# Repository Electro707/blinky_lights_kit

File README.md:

# Blinky Lights Kit

Welcome to the main repository for the Blinking Lights Kit. Here you will find everything that was used to make the project/kit come to life, from the KiCad file to the instruction's SVGs.

See [HERE](https://kits.electro707.com/blinky_lights/) for the project's page and documentation (including soldering instructions).

### Kit on Tindie
I am currently selling the kit on Tindie. The product page can be found at [https://www.tindie.com/products/20887/](https://www.tindie.com/products/20887/).

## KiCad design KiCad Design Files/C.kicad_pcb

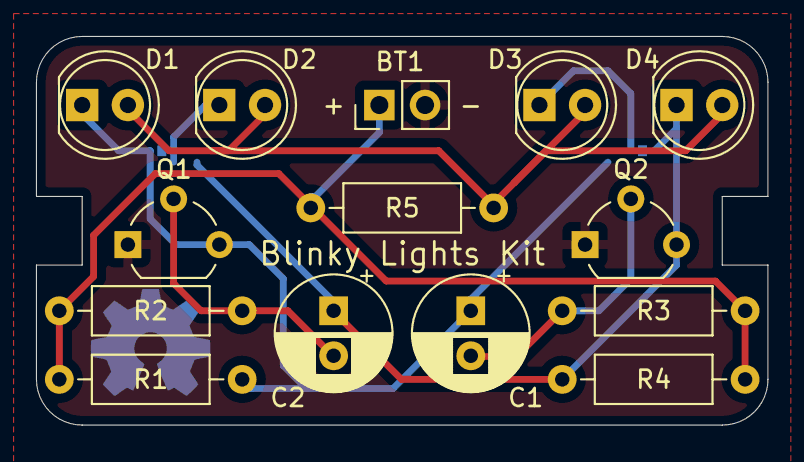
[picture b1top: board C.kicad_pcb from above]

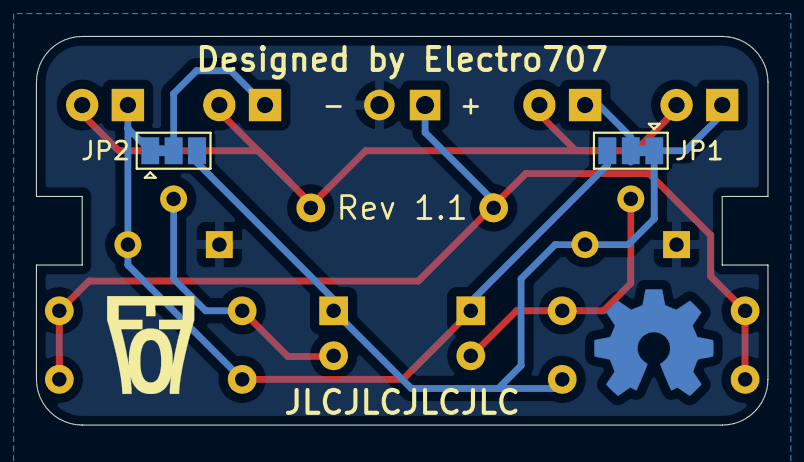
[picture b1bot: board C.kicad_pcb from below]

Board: 2 copper layers, 40.6 x 21.6 mm, 16 parts (2 on the bottom side), 9 nets.

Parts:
BT1: Battery; PinHeader_1x02_P2.54mm_Vertical
C1, C2: 100uF; CP_Radial_D6.3mm_P2.50mm
D1, D2, D3, D4: LED; LED_D5.0mm
JP1, JP2: SolderJumper_3_Bridged12; SolderJumper-3_P1.3mm_Bridged12_Pad1.0x1.5mm
Q1, Q2: 2N3904; TO-92_Wide
R1, R4: 270; R_Axial_DIN0207_L6.3mm_D2.5mm_P10.16mm_Horizontal
R2, R3: 10k; R_Axial_DIN0207_L6.3mm_D2.5mm_P10.16mm_Horizontal
R5: 1k; R_Axial_DIN0207_L6.3mm_D2.5mm_P10.16mm_Horizontal

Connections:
C1: C1.1, D1.1 (K), JP1.1 (A), JP2.3 (B), Q1.3 (C), R1.2
C2: C2.1, D4.1 (K), JP1.3 (B), JP2.1 (A), Q2.3 (C), R4.2
GND: BT1.2 (-), Q1.1 (E), Q2.1 (E)
unnamed: C1.2, Q2.2 (B), R3.2
unnamed: C2.2, Q1.2 (B), R2.2
unnamed: D1.2 (A), D2.2 (A), D3.2 (A), D4.2 (A), R5.2
unnamed: D2.1 (K), JP1.2 (C)
unnamed: D3.1 (K), JP2.2 (C)
VCC: BT1.1 (+), R1.1, R2.1, R3.1, R4.1, R5.1

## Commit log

2020-07-23 Changed README.md
2021-03-10 Oops, forgot to update the Tindie link (also added image on repo's page
2021-12-09 Updated schematic, 100k to 10k. Added right title block
2022-06-19 Updated files to KiCAD 6.0 and updated board to rev 1.1
    Rev 1.1 includes the following changes:
    - Minor silkscreen changes and component movement
    - Mainly changed the TO92 package to one which is easier to solder
2022-09-05 Updated Gerber files for Rev1.1. Added a car enclosure and assembly drawing
2022-09-06 Updated Rectangular enclosure and added STL files
2023-06-04 Added a JLCJLCJLCJLC silkscreen for ordering from JLC Removed Gerber and SVG files from git tracking KiCad updated some file's syntax and internal version to latest 6.x
